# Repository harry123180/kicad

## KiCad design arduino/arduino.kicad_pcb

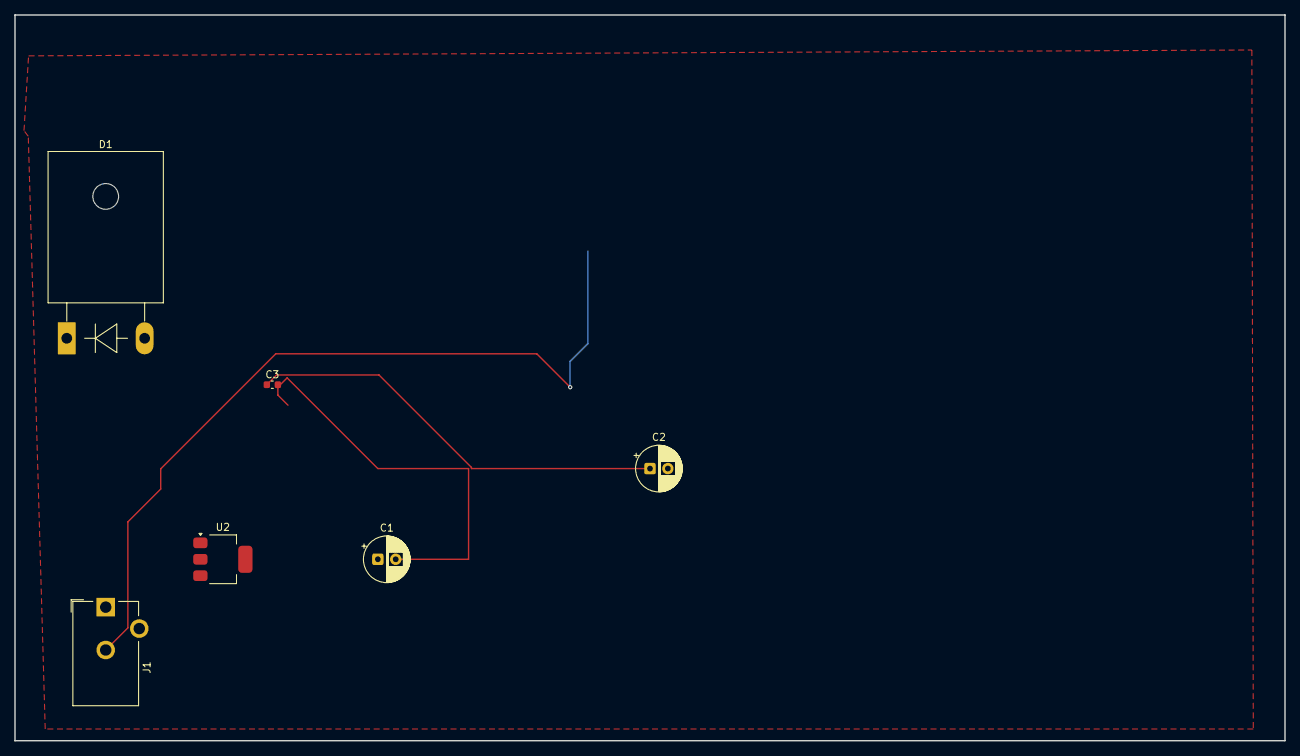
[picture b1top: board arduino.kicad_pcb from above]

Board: 4 copper layers, 177.8 x 101.6 mm, 7 parts (1 on the bottom side), 7 nets.

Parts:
C1, C2: C_Polarized; CP_Radial_D6.3mm_P2.50mm
C3: C; C_0603_1608Metric
D1: S2JTR; D_DO-247_Horizontal_TabDown
J1: POWERSUPPLY_DC21MMX; BarrelJack_CUI_PJ-102AH_Horizontal
U1: ATmega2560-16A; TQFP-100_14x14mm_P0.5mm
U2: LD1117S25TR_SOT223; SOT-223-3_TabPin2

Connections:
+5V: C1.1, U2.2 (VO)
/RESET: J1.2, U1.30 (~RESET)
GND: C1.2, C2.2, C3.2
unnamed: D1.2 (A), J1.1
unnamed: C2.1, C3.1, D1.1 (K), U2.3 (VI)
unnamed: U1.11 (GND), U1.32 (GND), U1.62 (GND), U1.81 (GND), U1.99 (GND)
unnamed: U1.10 (VCC), U1.31 (VCC), U1.61 (VCC), U1.80 (VCC)

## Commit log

2026-04-17 chore: ignore *.kicad_pcb to prevent tracking PCB layouts
2026-04-17 restore: arduino_mega2560_BOM.csv (62 components reference BOM)
